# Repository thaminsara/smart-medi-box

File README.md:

# smart-medi-box

**3d design**: `https://cad.onshape.com/documents/52d777575281a4c1dde482e8/w/16f7283f5e1f1f321381794d/e/75cd5e50e8d95697072f7eb7?renderMode=0&uiState=6a567d631745280725cee324`

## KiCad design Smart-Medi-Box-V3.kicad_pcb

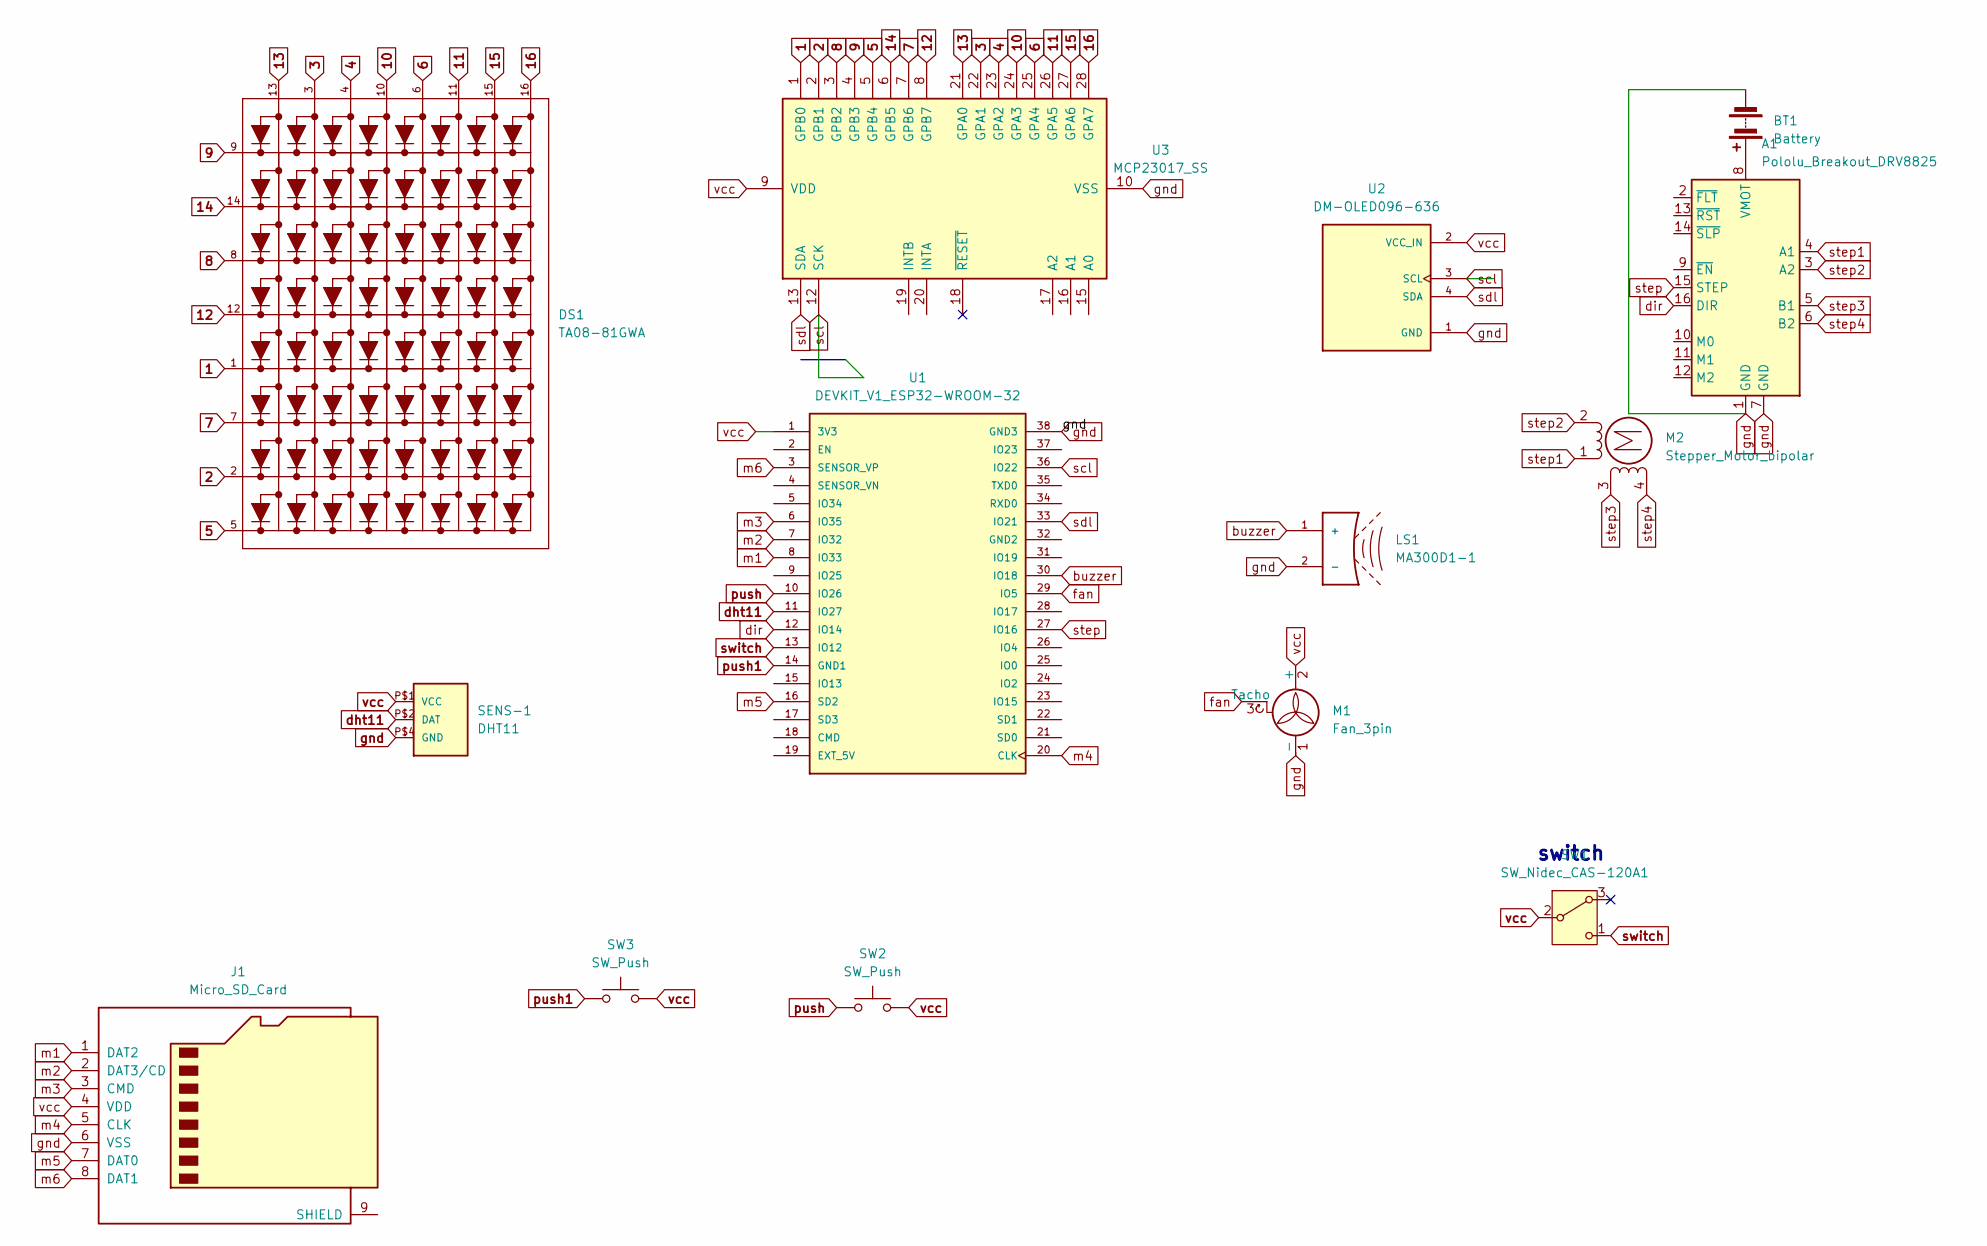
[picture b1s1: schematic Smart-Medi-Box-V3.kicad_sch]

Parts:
A1: Pololu_Breakout_DRV8825; Pololu_Breakout-16_15.2x20.3mm
BT1: Battery; BatteryHolder_Bulgin_BX0036_1xC
DS1: TA08-81GWA; DISPLAY_TA08-81GWA; PARTREV V.11A
J1: Micro_SD_Card; microSD_HC_Wuerth_693072010801
LS1: MA300D1-1; XDCR_MA300D1-1; PARTREV Q
M1: Fan_3pin; fan
M2: Stepper_Motor_bipolar; FanPinHeader_1x04_P2.54mm_Vertical
SENS-1: DHT11; SENSOR-DHT11
SW1: SW_Nidec_CAS-120A1; Nidec_Copal_CAS-120A
SW2, SW3: SW_Push; SW_Push_1TS009xxxx-xxxx-xxxx_6x6x5mm
U1: DEVKIT_V1_ESP32-WROOM-32; MODULE_DEVKIT_V1_ESP32-WROOM-32; PARTREV N/A
U2: DM-OLED096-636; MODULE_DM-OLED096-636; PARTREV 2018-09-10
U3: MCP23017_SS; SSOP-28_5.3x10.2mm_P0.65mm

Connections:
1: DS1.1, U3.1 (GPB0)
2: DS1.2, U3.2 (GPB1)
3: DS1.3, U3.22 (GPA1)
4: DS1.4, U3.23 (GPA2)
5: DS1.5, U3.5 (GPB4)
6: DS1.6, U3.25 (GPA4)
7: DS1.7, U3.7 (GPB6)
8: DS1.8, U3.3 (GPB2)
9: DS1.9, U3.4 (GPB3)
10: DS1.10, U3.24 (GPA3)
11: DS1.11, U3.26 (GPA5)
12: DS1.12, U3.8 (GPB7)
13: DS1.13, U3.21 (GPA0)
14: DS1.14, U3.6 (GPB5)
15: DS1.15, U3.27 (GPA6)
16: DS1.16, U3.28 (GPA7)
unnamed: A1.8 (VMOT), BT1.1 (+)
buzzer: LS1.1 (+), U1.30 (IO18)
dht11: SENS-1.P$2 (DAT), U1.11 (IO27)
dir: A1.16 (DIR), U1.12 (IO14)
fan: M1.3 (Tacho), U1.29 (IO5)
gnd: A1.1 (GND), A1.7 (GND), BT1.2 (-), J1.6 (VSS), LS1.2 (-), M1.1 (-), SENS-1.P$4 (GND), U1.38 (GND3), U2.1 (GND), U3.10 (VSS)
m1: J1.1 (DAT2), U1.8 (IO33)
m2: J1.2 (DAT3/CD), U1.7 (IO32)
m3: J1.3 (CMD), U1.6 (IO35)
m4: J1.5 (CLK), U1.20 (CLK)
m5: J1.7 (DAT0), U1.16 (SD2)
m6: J1.8 (DAT1), U1.3 (SENSOR_VP)
push: SW2.1, U1.10 (IO26)
push1: SW3.1, U1.14 (GND1)
scl: U1.36 (IO22), U2.3 (SCL), U3.12 (SCK)
sdl: U1.33 (IO21), U2.4 (SDA), U3.13 (SDA)
step: A1.15 (STEP), U1.27 (IO16)
step1: A1.4 (A1), M2.1
step2: A1.3 (A2), M2.2 (-)
step3: A1.5 (B1), M2.3
step4: A1.6 (B2), M2.4
switch: SW1.1 (C), U1.13 (IO12)
vcc: J1.4 (VDD), M1.2 (+), SENS-1.P$1 (VCC), SW1.2 (B), SW2.2, SW3.2, U1.1 (3V3), U2.2 (VCC_IN), U3.9 (VDD)

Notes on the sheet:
switch

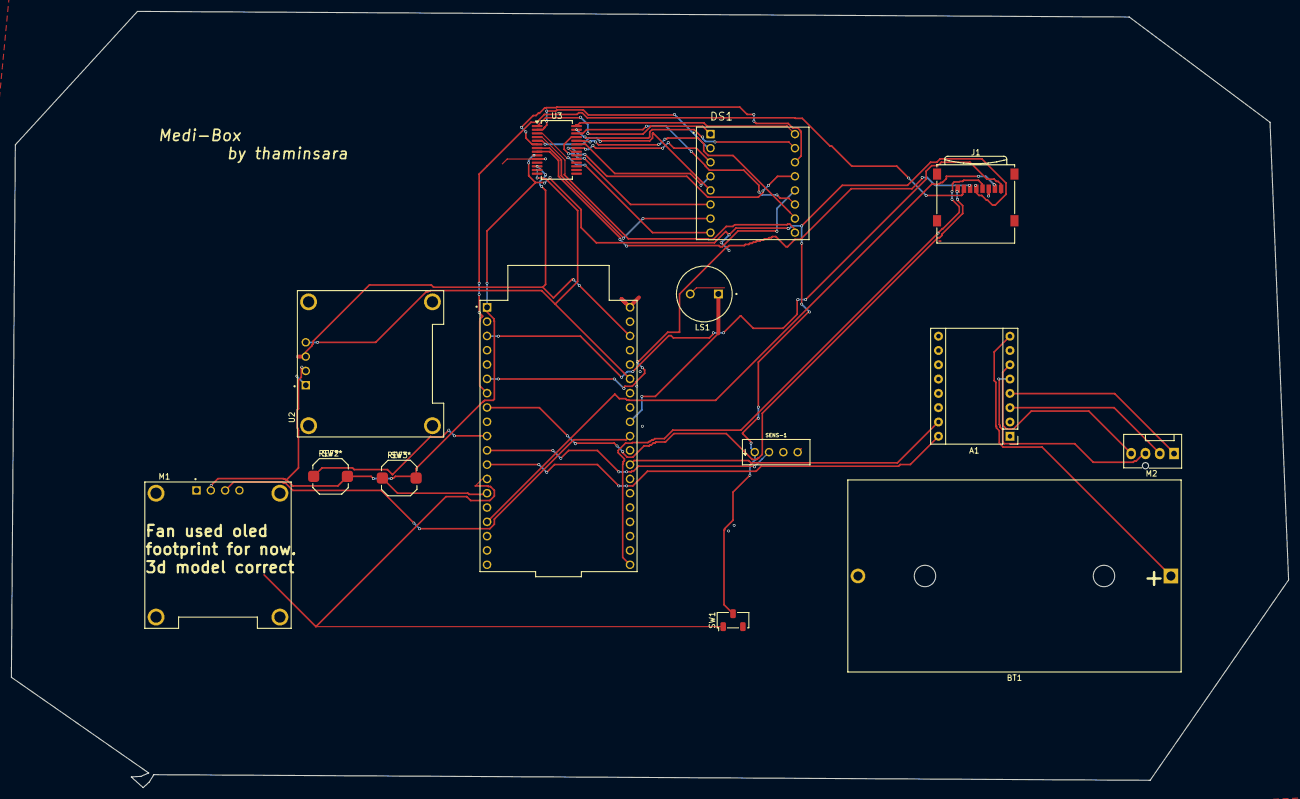
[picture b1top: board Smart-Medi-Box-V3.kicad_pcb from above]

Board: 2 copper layers, 226.9 x 137.9 mm, 14 parts (0 on the bottom side), 39 nets.
